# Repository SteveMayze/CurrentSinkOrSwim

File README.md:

# CurrentSinkOrSwim
Building a Current Sink for Battery Testing in Contextual Electronics.

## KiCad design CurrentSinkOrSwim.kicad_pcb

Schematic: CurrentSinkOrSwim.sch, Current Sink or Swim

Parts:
P101: CONN_01X03; Pin_Header_Straight_1x03; MPN M20-9990346
P102, P103: CONN_01X02; Terminal_Block_1x200_mil; MPN 50500020134G

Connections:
/Current Control/Current_Sink+: P101.3, P103.1; also elsewhere on the board
/Power Regulation/Vin: P101.2; also elsewhere on the board
GND: P102.2, P103.2; also elsewhere on the board
unnamed: P101.1, P102.1

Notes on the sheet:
Battery pack
Current sink input
Sheet 400 Series
Sheet 200 Series
Sheet 300 Series

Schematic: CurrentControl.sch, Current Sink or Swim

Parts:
C201: 0.1uF; SMD-0805
P201: HEATSINK; FA-220-38E; MPN FA-T220-38E
Q201: BUK9575; TO-220_FET-GDS_Vertical; MPN BUK9575-100A,127
R201: 1K; SMD-0805
R202: 68K; SMD-0805
R203: .1; Resistor_Vertical_RM5mm; MPN AC01000001007JA100
RV201: 10K; P090L-02F25BR10K; MPN P090L-02F25BR10K
U201: LMV358; MPN LMV358IDT

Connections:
2.7V: C201.1, R202.1, U201.8 (V+); also elsewhere on the board
/Current Control/Current_Sink+: Q201.2; also elsewhere on the board
/Current Control/FET_GATE: Q201.1, R201.1; also elsewhere on the board
GND: C201.2, R203.2, RV201.2, U201.4 (V-); also elsewhere on the board
unnamed: Q201.3, R203.1, U201.6 (-)
unnamed: R201.2, U201.7
unnamed: R202.2, RV201.1, U201.5 (+)

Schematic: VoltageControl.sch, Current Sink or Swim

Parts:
D301: 1N4148; SOD-523; MPN 1N4148WT
R301: 9K; SMD-0805
R302: 4k7; SMD-0805
R303: 1K; SMD-0805
RV301: 10K; P090L-02F25BR10K; MPN P090L-02F25BR10K
U201: LMV358; MPN LMV358IDT

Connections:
2.7V: R302.1, U201.8 (V+); also elsewhere on the board
/Current Control/Current_Sink+: R301.1; also elsewhere on the board
/Current Control/FET_GATE: D301.2; also elsewhere on the board
/Voltage Control/0-2v: R302.2, RV301.2, U201.3 (+)
/Voltage Control/0-2v_FeedBack: R301.2, R303.1, U201.2 (-)
GND: R303.2, RV301.3, U201.4 (V-); also elsewhere on the board
unnamed: D301.1, U201.1

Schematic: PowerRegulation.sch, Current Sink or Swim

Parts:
C401, C402: 0.1uF; SMD-0805
R401: 27k; SMD-0805
R402: 0; SMD-0805
R403: 21.6k; SMD-0805
U401: LM2931D-R; SOIC-8-N; MPN LM2931D-R

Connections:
2.7V: C402.1, R401.1, U401.1; also elsewhere on the board
/Power Regulation/Vin: C401.1, U401.8; also elsewhere on the board
GND: C401.2, C402.2, R402.2, R403.2, U401.2, U401.3, U401.6, U401.7; also elsewhere on the board
unnamed: R401.2, R403.1, U401.4
unnamed: R402.1, U401.5

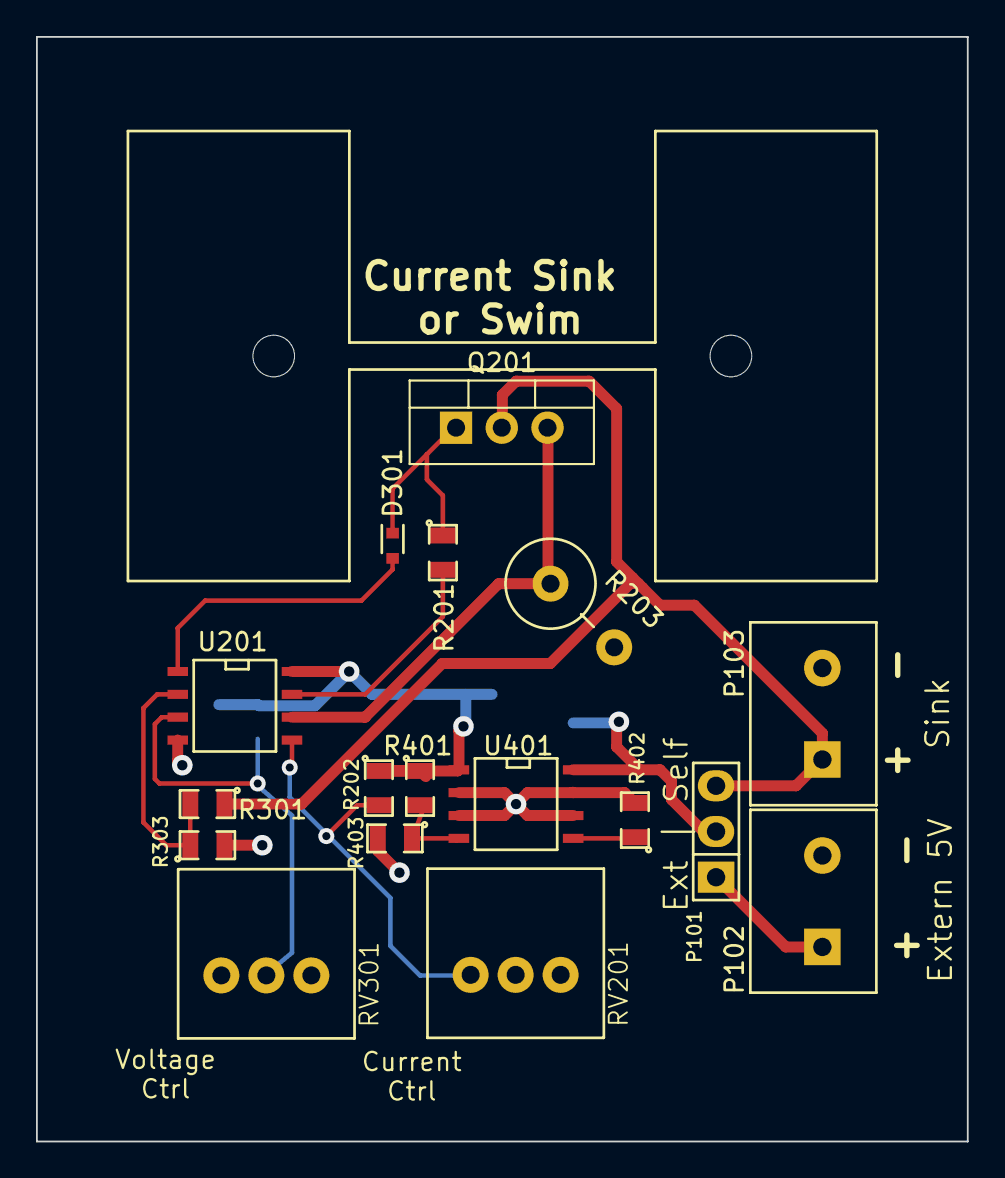
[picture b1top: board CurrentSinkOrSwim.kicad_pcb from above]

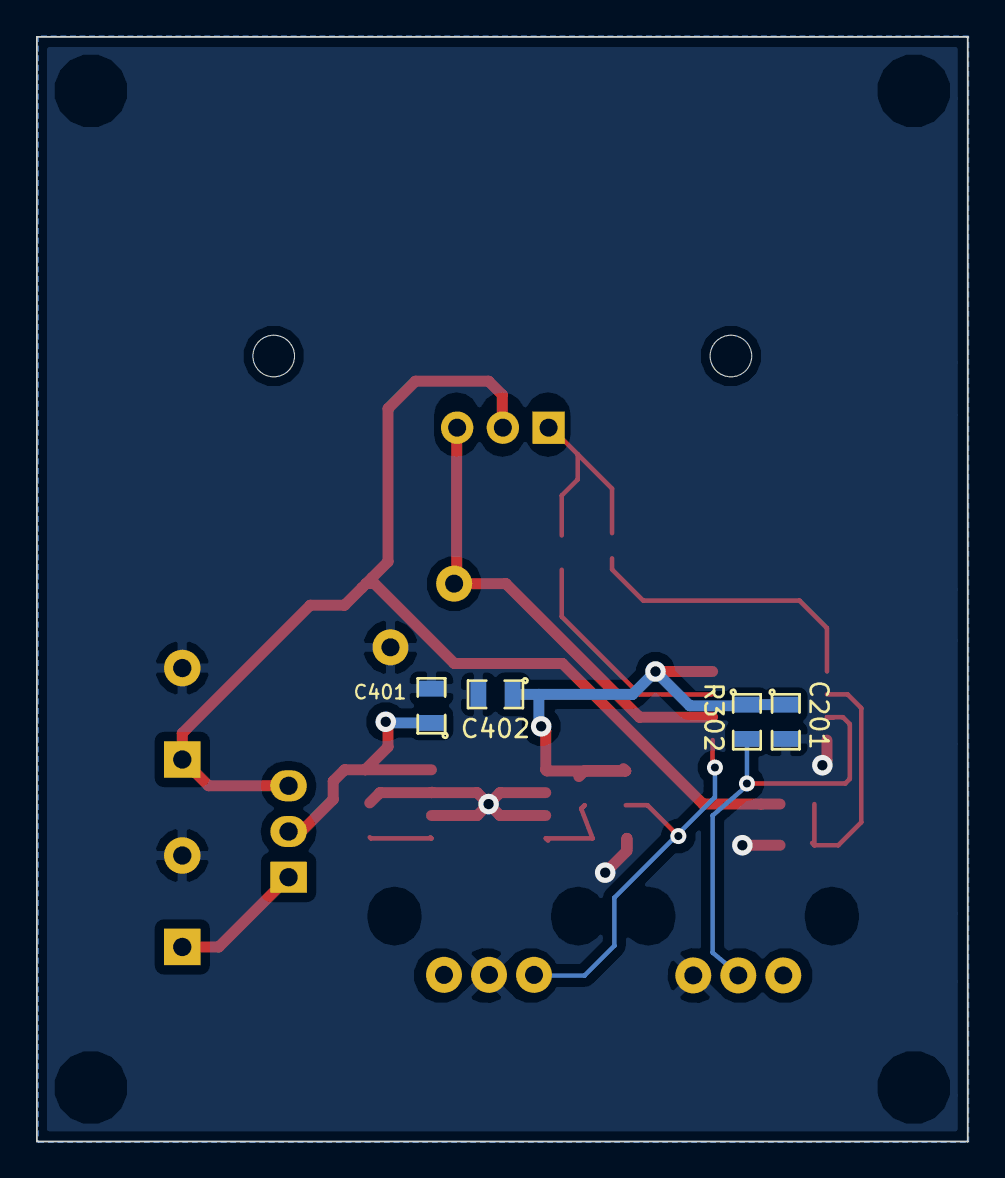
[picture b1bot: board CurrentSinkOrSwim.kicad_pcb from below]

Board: 2 copper layers, 51.7 x 61.4 mm, 22 parts (4 on the bottom side), 14 nets.

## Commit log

2015-02-01 KiCad project and schematic creation
2015-02-01 Added inital placements of components onto the PCB
2015-02-03 Corrections to schematic and .gitignore
2015-02-03 Removed the cache.lib from the project
2015-02-03 Updated the .gitignore to use ignore the -cache.lib file
2015-02-17 Small adjustments
2015-02-17 Caught up with video 18 - Linear Regulator
2015-02-17 Adding hierarchical sheets and voltage control circuit - Catching up with video 21
2015-02-17 Small correction
2015-02-17 Initial annotation
2015-02-17 Preliminary footprint association
2015-02-20 Rough board layout
2015-02-23 Updated the POT references and schematic
2015-02-23 Initial layout
2015-02-26 First cut of layout in preperation for the final session
2015-03-02 Routing and fixing schematic checkpoint
2015-03-02 Initial route before filling the ground plane
2015-03-02 Routed and filled board
2015-03-02 Added logo and fixed 3d view
2015-03-02 Gerber file creation
2015-03-03 Latest GERBER creation
2015-03-04 The gerbers are off to Fab.
2015-03-06 Final update to BOM and added the bom XSL script
2015-03-31 Corrected the default symbol changes in KiCad
2015-04-10 Added some test results
2015-04-12 Published the schematic PDF
2015-05-16 Adding LM239 datasheet
2015-09-15 Added a datasheet and initial user guide
2015-09-16 Result doc update
2015-09-16 Further updates to the data-sheet
2015-09-30 Updates to the datasheet
2015-09-30 Added 3mm mounting hole and added board improvements
2015-11-22 Updated the documentation
2020-09-15 Updates to the libraries for the lastest KiCad and a small update to the Datasheet
2020-09-26 Parts update
2020-09-26 Board update and corrections
2020-09-27 Playing with Fritzing for some connection diagrams
